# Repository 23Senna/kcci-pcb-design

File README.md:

# KCCI PCB Design Portfolio

PCB design work by **Bramantio Ananda** (Electrical Engineering, Institut Teknologi Bandung) during the
**KCCI Overseas Professional Technical Workforce Training Program – Electronics track**.
All boards were designed in **KiCad 10** from schematic capture through routing, DRC, and fabrication output.

| Project | Layers | Size | Highlights |
|---|---|---|---|
| [**ESP32-P4 MIPI-DSI → HDMI / LVDS Bridge**](hdmi-lvds-bridge/) | 4 | 65.4 × 49.2 mm | LT8912B bridge, 100 Ω controlled-impedance pairs, length-matched DSI / TMDS / LVDS, double-sided assembly |
| [**ATmega128-16A Minimum System**](atmega128-minimum-system/) | 2 | 71.6 × 46.3 mm | TQFP-64 MCU, 5 V linear regulator, ISP header, all ports broken out |
| [**Conveyor Sorter Shield** (group project)](conveyor-shield-kel1/) | 2 | — | STM32 Nucleo-F411RE shield with buck converter and actuator connectors |
| [**Signal-Integrity Analyses**](signal-integrity/) | — | — | Crosstalk, backplane channel, and CTLE studies (MATLAB, Serial Link Designer, SPICE) |

## Repository layout

Each board folder follows the same structure:

```
<project>/
├── kicad/            KiCad project (.kicad_pro / .kicad_sch / .kicad_pcb) + project-local libraries
├── fabrication/
│   ├── gerber/       Gerber + Excellon drill files (ready to upload to a PCB fab)
│   └── assembly/     BOM (.csv) and pick-and-place (.pos)
└── docs/             Schematic PDF and board renders
```

## Opening the projects

1. Install [KiCad 10](https://www.kicad.org/download/) (files were saved with KiCad 10.0.7; older versions cannot open them).
2. Open `<project>/kicad/*.kicad_pro`.
   Custom symbols and footprints are included in each project's `kicad/library` folder and registered in the
   project-local `sym-lib-table` / `fp-lib-table`, so no extra library setup is needed.

## Author

Bramantio Ananda · [Portfolio](https://bramantio-ananda-portfolio.netlify.app/) · [GitHub @23Senna](https://github.com/23Senna)

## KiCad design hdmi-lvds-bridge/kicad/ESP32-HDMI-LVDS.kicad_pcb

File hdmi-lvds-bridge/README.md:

# ESP32-P4 MIPI-DSI → HDMI / LVDS Bridge

A 4-layer converter board that takes the **2-lane MIPI-DSI** display output of an **ESP32-P4** and drives either an
**HDMI** monitor or an **LVDS** panel, using the **Lontium LT8912B** bridge IC.

<p align="center"><sub>Top and bottom renders generated from the fabrication Gerbers.</sub></p>

## Block diagram

```mermaid
flowchart LR
    P4["ESP32-P4<br/>(MIPI-DSI host)"] -- "DSI CLK + D0/D1<br/>FFC J3" --> U2["LT8912B<br/>MIPI → HDMI/LVDS"]
    P4 -- "I²C · INT · RSTN · I²S<br/>(3.3 V)" --> LS["BSS138<br/>level shifters"] -- "1.8 V" --> U2
    U2 -- "TMDS CLK + D0–D2" --> ESD["RClamp0524P<br/>ESD"] --> J4["HDMI Type-A<br/>J4"]
    U2 -- "LVDS CLK + D0–D3" --> J2["LVDS header<br/>J2 (2×9)"]
    P4 -- "3.3 V" --> LDO["SGM2212<br/>1.8 V LDO"] -- "ferrite-isolated rails" --> U2
    J1["J1 · 5 V in"] --> D2["Schottky<br/>reverse protection"] -- "HDMI 5 V" --> J4
```

## Specifications

| Item | Value |
|---|---|
| Board size | 65.4 × 49.2 mm, 1.6 mm FR-4 |
| Stack-up | 4 layers – **F.Cu signal / In1 GND / In2 GND / B.Cu signal** (JLCPCB JLC04161H-7628, prepreg 0.21 mm, εr ≈ 4.4) |
| Components | 96 placements – 61 top, 35 bottom (double-sided assembly) |
| Differential pairs | 100 Ω: 0.1278 mm width / 0.127 mm gap (from JLCPCB impedance calculator) |
| Signal / power tracks | 0.2 mm (0.15 mm at QFN pins) / 0.5 mm |
| Vias | 0.6 mm pad / 0.3 mm drill |
| Min. clearance · copper-to-edge | 0.127 mm · 0.5 mm |

### Length matching (custom DRC rules in `ESP32-HDMI-LVDS.kicad_dru`)

| Interface | Pairs | Target length | Intra-pair skew |
|---|---|---|---|
| MIPI-DSI (J3 → LT8912B) | CLK, D0, D1 | 71.74 mm (±0.05) | ≤ 0.07 mm |
| HDMI TMDS (LT8912B → J4) | CLK, D0, D1, D2 | 12.76 mm (±0.14) | ≤ 0.10 mm |
| LVDS (LT8912B → J2) | CLK, D0–D3 | 18.70 mm (±0.04) | ≤ 0.04 mm |

All high-speed pairs run over the solid inner ground planes.

## Design notes

- **Power:** an SGM2212 LDO derives 1.8 V for the LT8912B from the ESP32-P4's 3.3 V rail, and each analog/digital/PLL rail
  is isolated with a 220 Ω @ 100 MHz ferrite bead plus 10 µF / 0.1 µF decoupling. 5 V enters on J1 through a 1N5819
  Schottky (reverse-polarity protection) and supplies the HDMI +5 V / DDC side.
  The decoupling capacitors sit on the bottom side directly under U2.
- **Clock and PLL:** 25 MHz crystal (10 pF load caps, 1 MΩ bias), 6.04 kΩ R6K bias resistor, and a 2.2 nF HDMI-PLL
  loop-filter capacitor on PLL_LPF (pin 35).
- **Control signals:** BSS138 bidirectional shifters translate I²C, INT, RSTN, and I²S between the ESP32-P4 (3.3 V) and the
  LT8912B (1.8 V). HDMI DDC is shifted to the 5 V HDMI side, and HPD is level-shifted through an MMBT3904.
- **Protection:** RClamp0524P TVS arrays on all TMDS lines at the HDMI connector.

## Files

| Path | Contents |
|---|---|
| [`kicad/`](kicad/) | KiCad 10 project, custom DRC rules, project-local symbol / footprint / 3D libraries |
| [`fabrication/gerber/`](fabrication/gerber/) | Gerbers (F/In1/In2/B copper, mask, paste, silk, edge) and PTH / NPTH drill files |
| [`fabrication/assembly/`](fabrication/assembly/) | BOM (`ESP32-HDMI-LVDS-BOM.csv`) and pick-and-place (`ESP32-HDMI-LVDS-all.pos`) |
| [`docs/`](docs/) | Schematic PDF (exported 2026-10-15) and board renders |

**Status:** design complete, DRC-clean in KiCad 10.

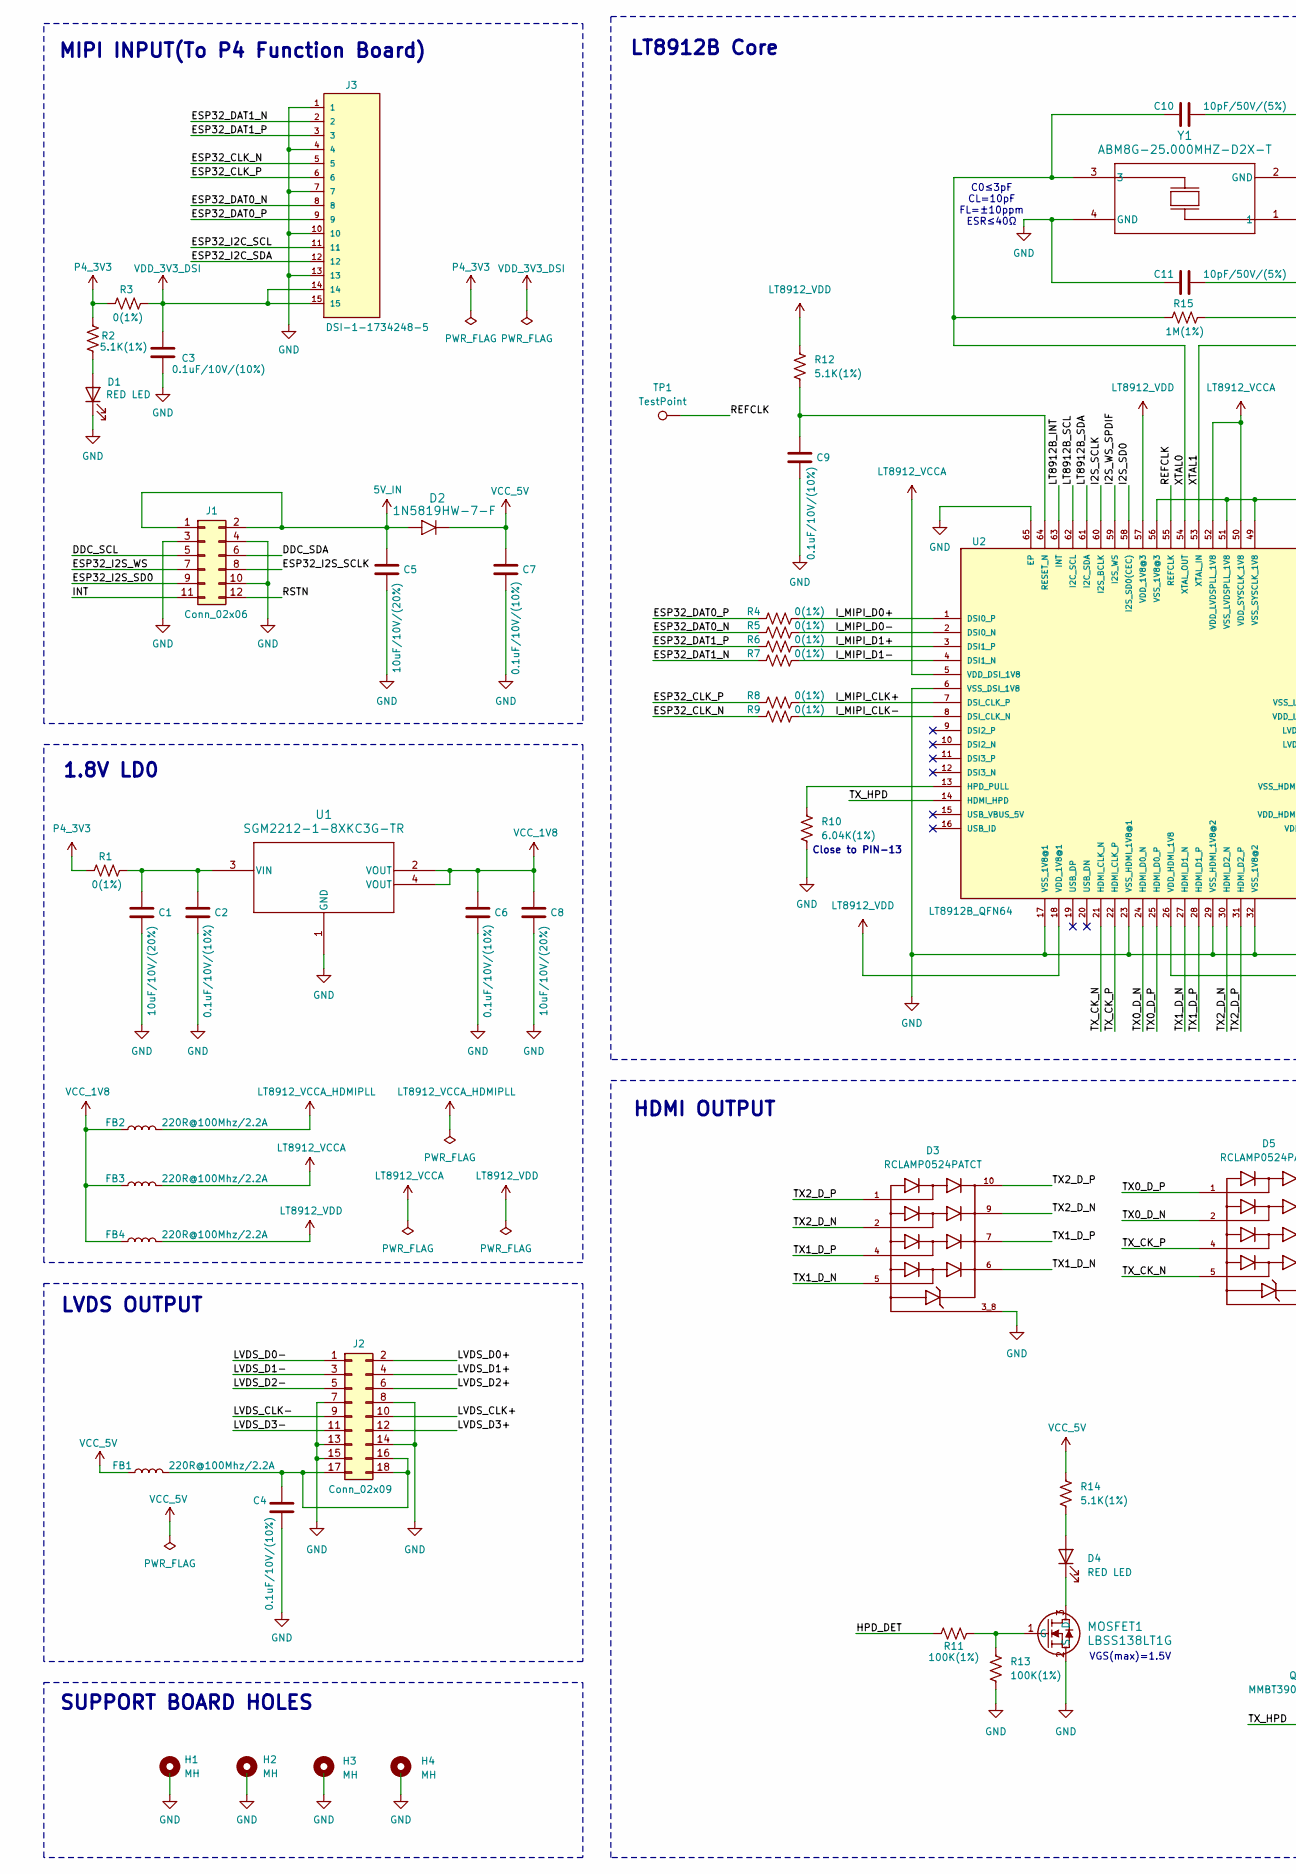
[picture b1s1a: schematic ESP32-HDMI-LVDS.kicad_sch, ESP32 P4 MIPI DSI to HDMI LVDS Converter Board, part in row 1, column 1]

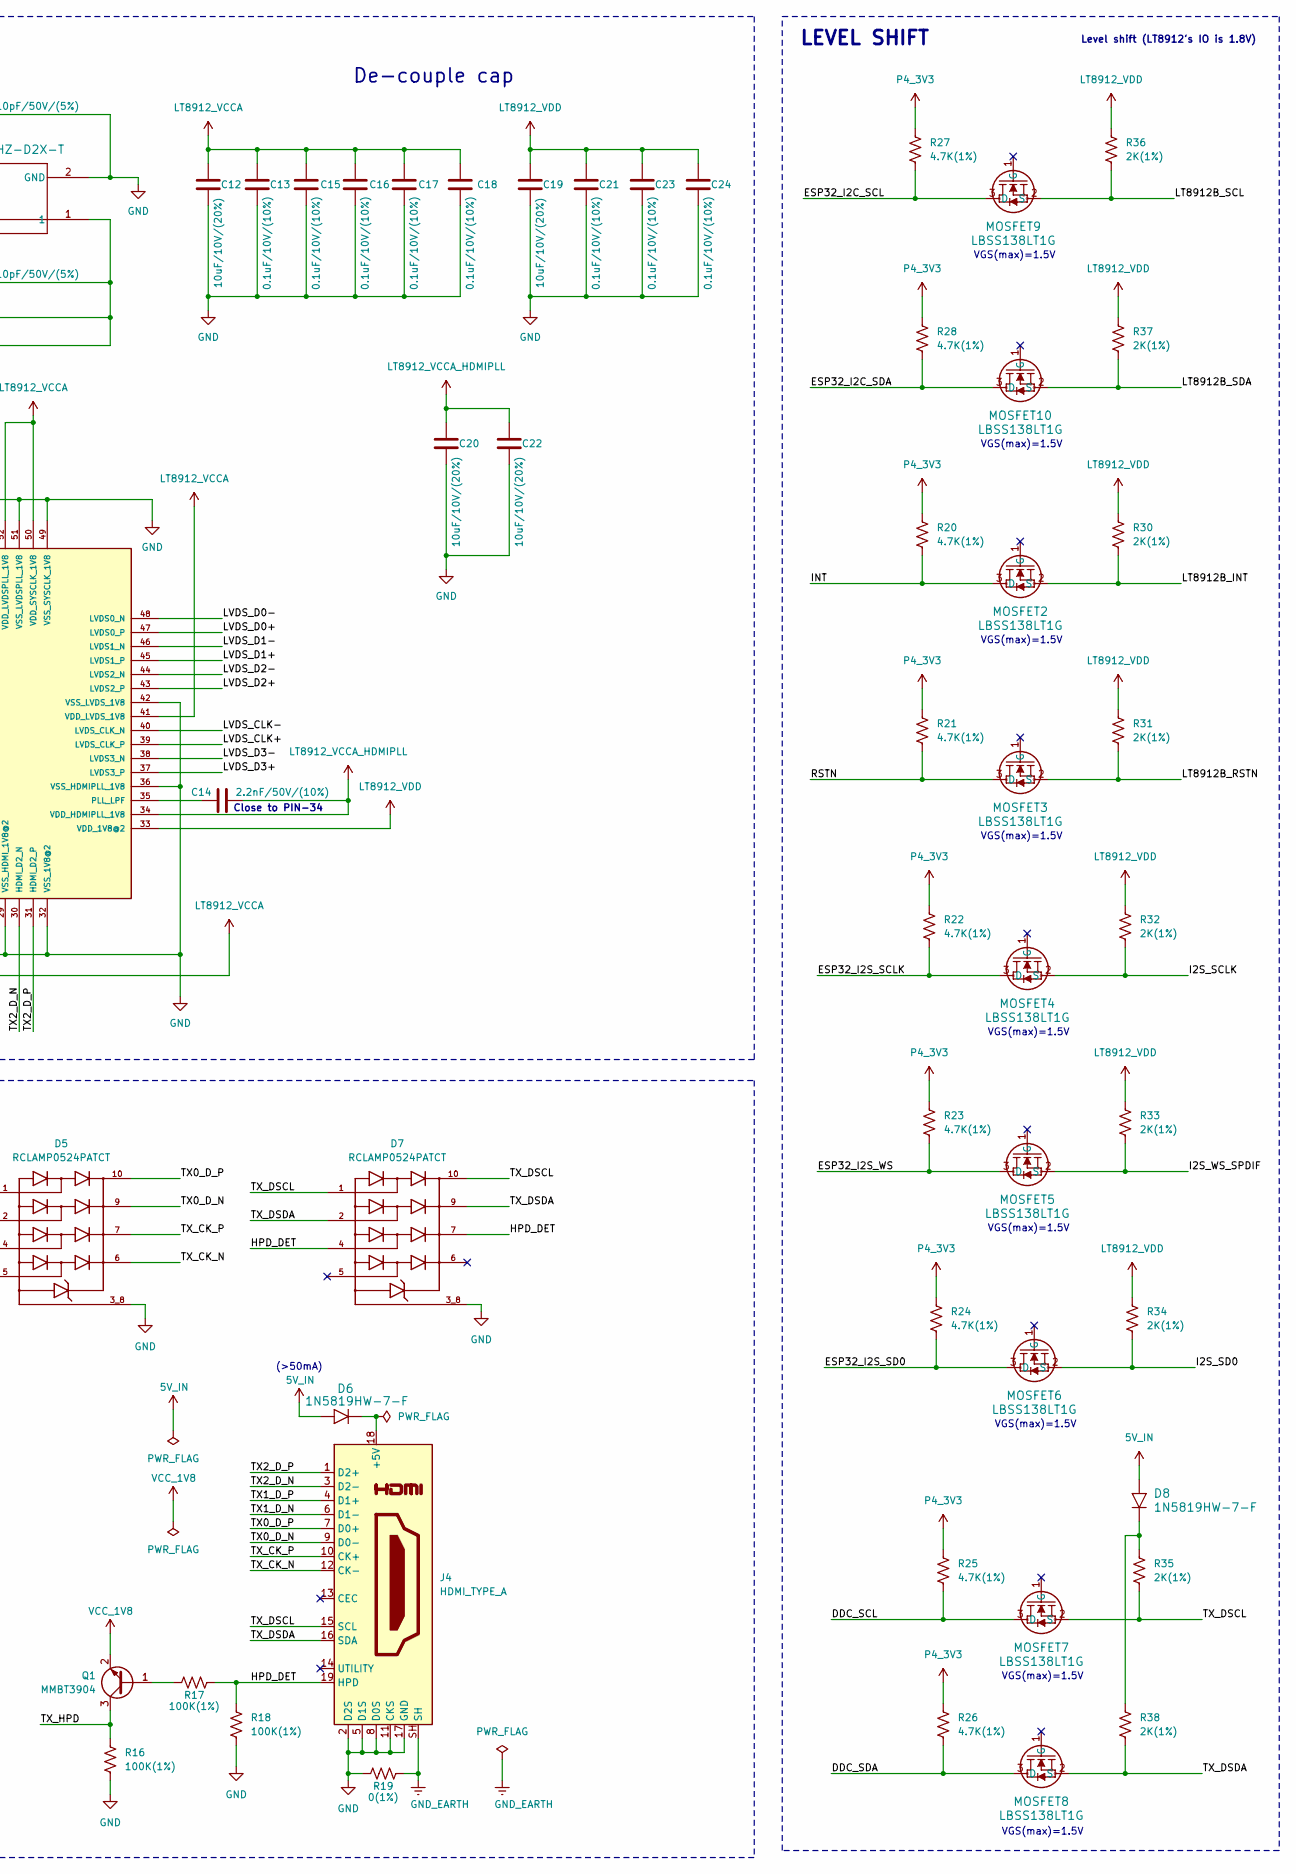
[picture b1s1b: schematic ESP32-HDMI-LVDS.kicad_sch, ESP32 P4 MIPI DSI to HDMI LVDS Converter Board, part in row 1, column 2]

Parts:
C1, C5, C8, C12, C19, C20, C22: 10uF/10V/(20%); C_0603_1608Metric_Pad1.08x0.95mm_HandSolder
C2, C3, C4, C6, C7, C9, C13, C15, C16, C17, C18, C21, C23, C24: 0.1uF/10V/(10%); C_0603_1608Metric_Pad1.08x0.95mm_HandSolder
C10, C11: 10pF/50V/(5%); C_0603_1608Metric_Pad1.08x0.95mm_HandSolder
C14: 2.2nF/50V/(10%); C_0603_1608Metric_Pad1.08x0.95mm_HandSolder
D1, D4: RED LED; LED_0603_1608Metric_Pad1.05x0.95mm_HandSolder
D2, D6, D8: 1N5819HW-7-F; 1N5819HW-7-F_DIO
D3, D5, D7: RCLAMP0524PATCT; DIO_RCLAMP0524PATCT; PARTREV 2/23/2011
FB1, FB2, FB3, FB4: 220R@100Mhz/2.2A; L_0603_1608Metric_Pad1.05x0.95mm_HandSolder
H1, H2, H3, H4: MH; MountingHole_3.2mm_M3_Pad_TopBottom
J1: Conn_02x06; PinHeader_2x06_P2.54mm_Vertical
J2: Conn_02x09; PinHeader_2x09_P2.54mm_Vertical
J3: DSI-1-1734248-5; TE_1-1734248-5; PARTREV E1
J4: HDMI_TYPE_A; HDMI_A_Molex_208658-1001_Horizontal
MOSFET1, MOSFET2, MOSFET3, MOSFET4, MOSFET5, MOSFET6, MOSFET7, MOSFET8, MOSFET9, MOSFET10: LBSS138LT1G; SOT23_TO-236_LRC
Q1: MMBT3904; SOT-23
R1, R3, R4, R5, R6, R7, R8, R9, R19: 0(1%); R_0603_1608Metric_Pad0.98x0.95mm_HandSolder
R2, R12, R14: 5.1K(1%); R_0603_1608Metric_Pad0.98x0.95mm_HandSolder
R10: 6.04K(1%); R_0603_1608Metric_Pad0.98x0.95mm_HandSolder
R11, R13, R16, R17, R18: 100K(1%); R_0603_1608Metric_Pad0.98x0.95mm_HandSolder
R15: 1M(1%); R_0603_1608Metric_Pad0.98x0.95mm_HandSolder
R20, R21, R22, R23, R24, R25, R26, R27, R28: 4.7K(1%); R_0603_1608Metric_Pad0.98x0.95mm_HandSolder
R30, R31, R32, R33, R34, R35, R36, R37, R38: 2K(1%); R_0603_1608Metric_Pad0.98x0.95mm_HandSolder
TP1: TestPoint; TestPoint_Pad_D1.0mm
U1: SGM2212-1-8XKC3G-TR; SOT-223-3_SGM2212_SNC
U2: LT8912B_QFN64; LT8912B
Y1: ABM8G-25.000MHZ-D2X-T; CRYSTAL_ABM8G_ABR

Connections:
5V_IN: C5.2, D2.1 (A), D6.1 (A), D8.1 (A), J1.1, J1.2
/DDC_SCL: J1.5, MOSFET7.3 (D), R25.2
/DDC_SDA: J1.6, MOSFET8.3 (D), R26.2
/ESP32_CLK_N: J3.5, J3.5_1 (5), R9.1
/ESP32_CLK_P: J3.6, J3.6_1 (6), R8.1
/ESP32_DAT0_N: J3.8, J3.8_1 (8), R5.1
/ESP32_DAT0_P: J3.9, J3.9_1 (9), R4.1
/ESP32_DAT1_N: J3.2, J3.2_1 (2), R7.1
/ESP32_DAT1_P: J3.3, J3.3_1 (3), R6.1
/ESP32_I2C_SCL: J3.11, J3.11_1 (11), MOSFET9.3 (D), R27.2
/ESP32_I2C_SDA: J3.12, J3.12_1 (12), MOSFET10.3 (D), R28.2
/ESP32_I2S_SCLK: J1.8, MOSFET4.3 (D), R22.2
/ESP32_I2S_SD0: J1.9, MOSFET6.3 (D), R24.2
/ESP32_I2S_WS: J1.7, MOSFET5.3 (D), R23.2
/HPD_DET: D7.4, D7.7, J4.19 (HPD), R11.1, R17.2, R18.1
/I2S_SCLK: MOSFET4.2 (S), R32.2, U2.60 (I2S_BCLK)
/I2S_SD0: MOSFET6.2 (S), R34.2, U2.58 (I2S_SD0(CEC))
/I2S_WS_SPDIF: MOSFET5.2 (S), R33.2, U2.59 (I2S_WS)
/INT: J1.11, MOSFET2.3 (D), R20.2
/I_MIPI_CLK+: R8.2, U2.7 (DSI_CLK_P)
/I_MIPI_CLK-: R9.2, U2.8 (DSI_CLK_N)
/I_MIPI_D0+: R4.2, U2.1 (DSI0_P)
/I_MIPI_D0-: R5.2, U2.2 (DSI0_N)
/I_MIPI_D1+: R6.2, U2.3 (DSI1_P)
/I_MIPI_D1-: R7.2, U2.4 (DSI1_N)
/LT8912B_INT: MOSFET2.2 (S), R30.2, U2.63 (INT)
/LT8912B_RSTN: MOSFET3.2 (S), R31.2
/LT8912B_SCL: MOSFET9.2 (S), R36.2, U2.62 (I2C_SCL)
/LT8912B_SDA: MOSFET10.2 (S), R37.2, U2.61 (I2C_SDA)
/LVDS_CLK+: J2.10, U2.39 (LVDS_CLK_P)
/LVDS_CLK-: J2.9, U2.40 (LVDS_CLK_N)
/LVDS_D0+: J2.2, U2.47 (LVDS0_P)
/LVDS_D0-: J2.1, U2.48 (LVDS0_N)
/LVDS_D1+: J2.4, U2.45 (LVDS1_P)
/LVDS_D1-: J2.3, U2.46 (LVDS1_N)
/LVDS_D2+: J2.6, U2.43 (LVDS2_P)
/LVDS_D2-: J2.5, U2.44 (LVDS2_N)
/LVDS_D3+: J2.12, U2.37 (LVDS3_P)
/LVDS_D3-: J2.11, U2.38 (LVDS3_N)
/REFCLK: TP1.1 (1_1), U2.55 (REFCLK)
/RSTN: J1.12, MOSFET3.3 (D), R21.2
/TX0_D_N: D5.2, D5.9, J4.9 (D0-), U2.24 (HDMI_D0_N)
/TX0_D_P: D5.1, D5.10, J4.7 (D0+), U2.25 (HDMI_D0_P)
/TX1_D_N: D3.5, D3.6, J4.6 (D1-), U2.27 (HDMI_D1_N)
/TX1_D_P: D3.4, D3.7, J4.4 (D1+), U2.28 (HDMI_D1_P)
/TX2_D_N: D3.2, D3.9, J4.3 (D2-), U2.30 (HDMI_D2_N)
/TX2_D_P: D3.1, D3.10, J4.1 (D2+), U2.31 (HDMI_D2_P)
/TX_CK_N: D5.5, D5.6, J4.12 (CK-), U2.21 (HDMI_CLK_N)
/TX_CK_P: D5.4, D5.7, J4.10 (CK+), U2.22 (HDMI_CLK_P)
/TX_DSCL: D7.1, D7.10, J4.15 (SCL), MOSFET7.2 (S), R35.2
/TX_DSDA: D7.2, D7.9, J4.16 (SDA), MOSFET8.2 (S), R38.2
/TX_HPD: Q1.3 (C), R16.1, U2.14 (HDMI_HPD)
/XTAL0: C10.1, R15.1, U2.54 (XTAL_OUT), Y1.3
/XTAL1: C11.2, R15.2, U2.53 (XTAL_IN), Y1.1
GND: C1.1, C2.1, C3.2, C4.2, C5.1, C6.1, C7.1, C8.1, C9.1, C10.2, C11.1, C12.1, C13.1, C15.1, C16.1, C17.1, C18.1, C19.1, C20.1, C21.1, C22.1, C23.1, C24.1, D1.1 (K), D3.3_8, D5.3_8, D7.3_8, J1.3, J1.4, J1.10, J2.7, J2.8, J2.13, J2.14, J2.15, J3.1, J3.1_1 (1), J3.4, J3.4_1 (4), J3.7, J3.7_1 (7), J3.10, J3.10_1 (10), J3.13, J3.13_1 (13), J4.2 (D2S), J4.5 (D1S), J4.8 (D0S), J4.11 (CKS), J4.17 (GND), MOSFET1.2 (S), R10.2, R13.2, R16.2, R18.2, R19.1, U1.1 (GND), U2.6 (VSS_DSI_1V8), U2.17 (VSS_1V8@1), U2.23 (VSS_HDMI_1V8@1), U2.29 (VSS_HDMI_1V8@2), U2.32 (VSS_1V8@2), U2.36 (VSS_HDMIPLL_1V8), U2.42 (VSS_LVDS_1V8), U2.49 (VSS_SYSCLK_1V8), U2.51 (VSS_LVDSPLL_1V8), U2.56 (VSS_1V8@3), U2.65 (EP), Y1.2 (GND), Y1.4 (GND)
GND_EARTH: J4.SH, R19.2
LT8912_VCCA: C12.2, C13.2, C15.2, C16.2, C17.2, C18.2, FB3.2, U2.5 (VDD_DSI_1V8), U2.26 (VDD_HDMI_1V8), U2.41 (VDD_LVDS_1V8), U2.50 (VDD_SYSCLK_1V8), U2.52 (VDD_LVDSPLL_1V8)
LT8912_VCCA_HDMIPLL: C14.2, C20.2, C22.2, FB2.2, U2.34 (VDD_HDMIPLL_1V8)
LT8912_VDD: C19.2, C21.2, C23.2, C24.2, FB4.2, R12.1, R30.1, R31.1, R32.1, R33.1, R34.1, R36.1, R37.1, U2.18 (VDD_1V8@1), U2.33 (VDD_1V8@2), U2.57 (VDD_1V8@3)
unnamed: D1.2 (A), R2.2
unnamed: D4.2 (A), R14.2
unnamed: D4.1 (K), MOSFET1.3 (D)
unnamed: D6.2 (K), J4.18 (+5V)
unnamed: D8.2 (K), R35.1, R38.1
unnamed: C4.1, FB1.2, J2.16, J2.17, J2.18
unnamed: MOSFET1.1 (G), R11.2, R13.1
unnamed: Q1.1 (B), R17.1
unnamed: C1.2, C2.2, R1.2, U1.3 (VIN)
unnamed: R10.1, U2.13 (HPD_PULL)
unnamed: C14.1, U2.35 (PLL_LPF)
unnamed: C9.2, R12.2, U2.64 (RESET_N)
P4_3V3: R1.1, R2.1, R3.1, R20.1, R21.1, R22.1, R23.1, R24.1, R25.1, R26.1, R27.1, R28.1
VCC_1V8: C6.2, C8.2, FB2.1, FB3.1, FB4.1, Q1.2 (E), U1.2 (VOUT), U1.4 (VOUT)
VCC_5V: C7.2, D2.2 (K), FB1.1, R14.1
VDD_3V3_DSI: C3.1, J3.14, J3.14_1 (14), J3.15, J3.15_1 (15), R3.2

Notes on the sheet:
HDMI OUTPUT
VGS(max)=1.5V
Level shift (LT8912's IO is 1.8V)
Close to PIN-13
1.8V LD0
(>50mA)
Close to PIN-34
De-couple cap
LT8912B Core
C0≤3pF CL=10pF FL=±10ppm ESR≤40Ω
SUPPORT BOARD HOLES
MIPI INPUT(To P4 Function Board)
LVDS OUTPUT
LEVEL SHIFT

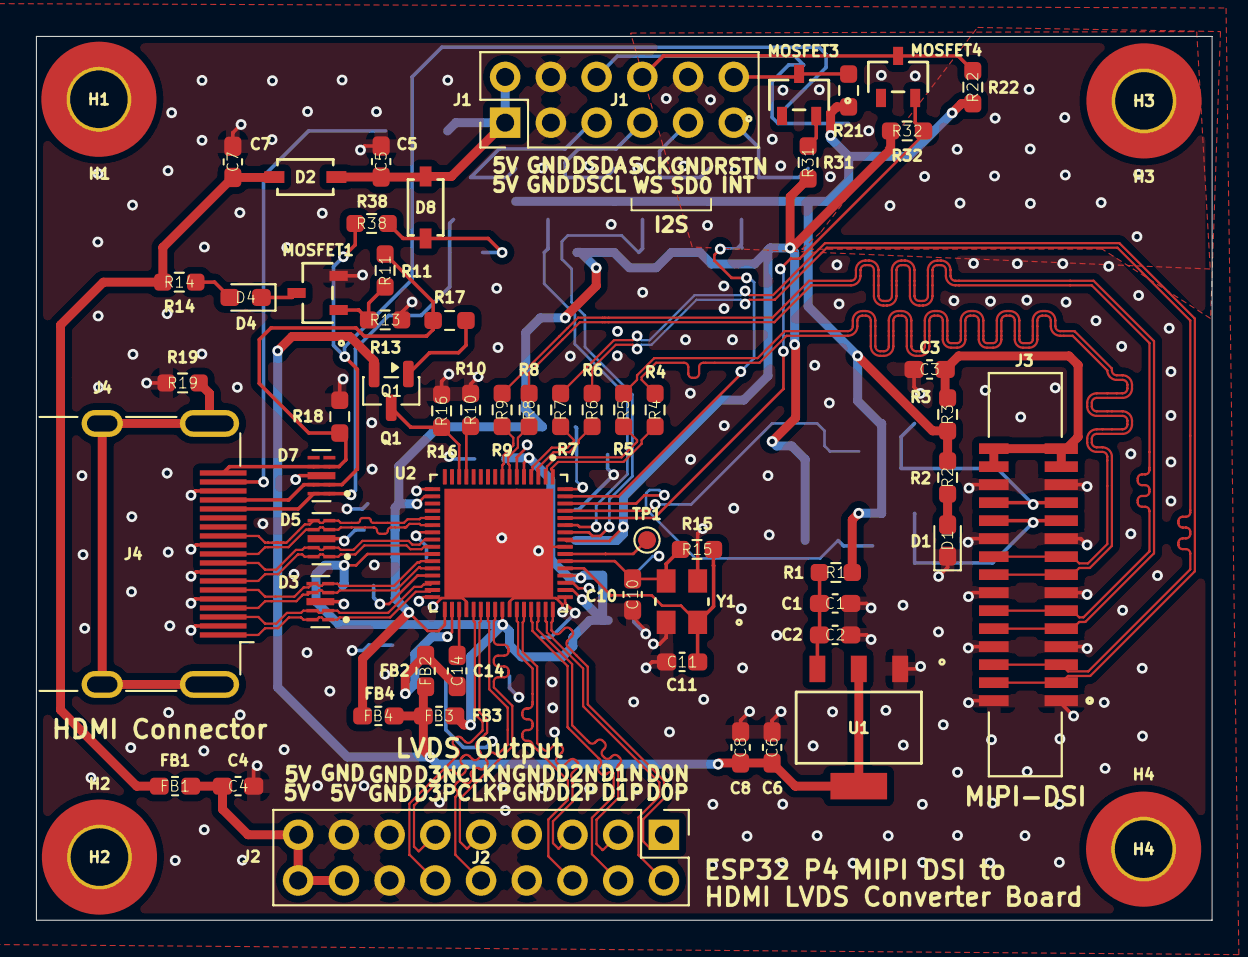
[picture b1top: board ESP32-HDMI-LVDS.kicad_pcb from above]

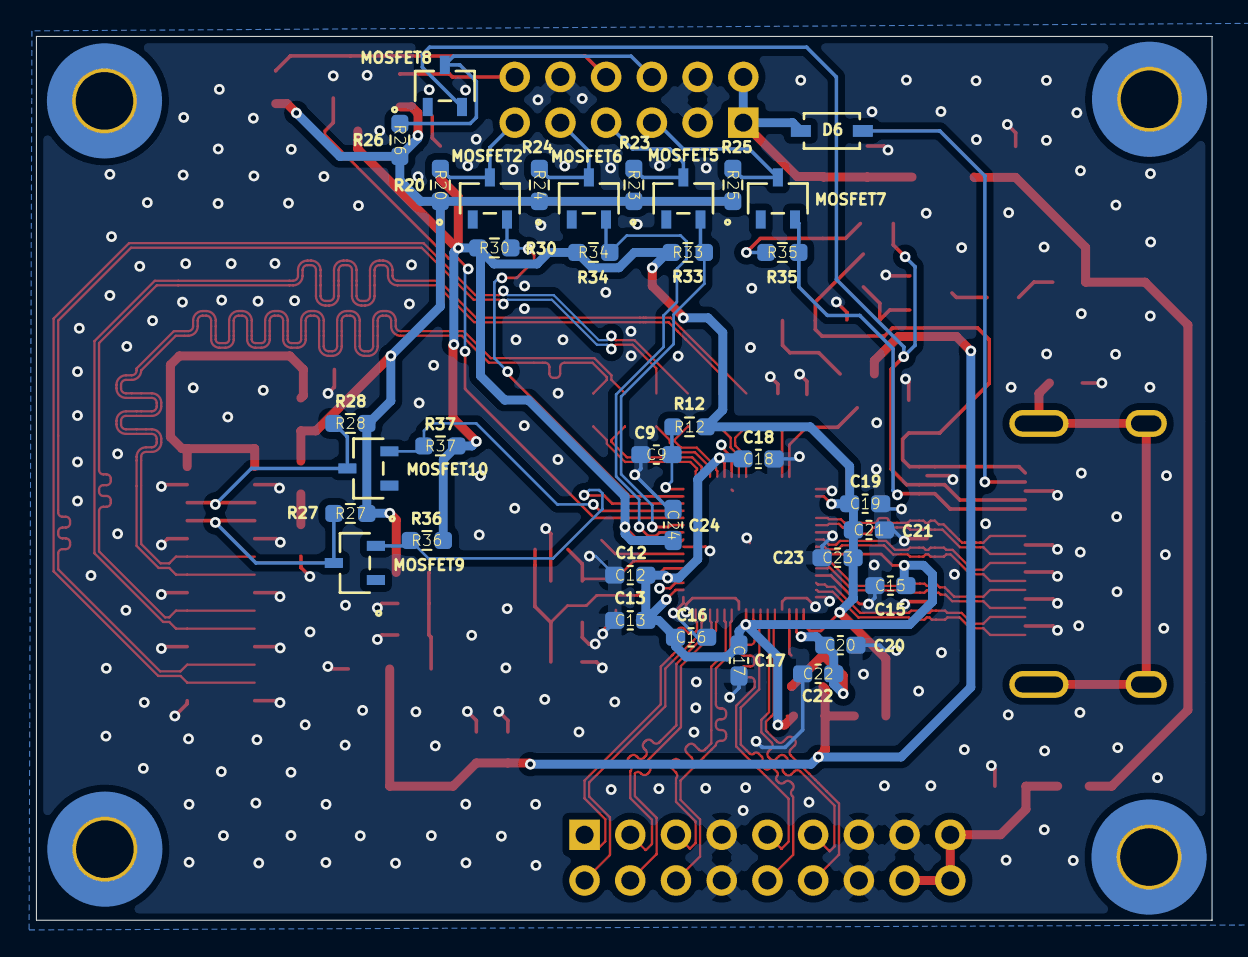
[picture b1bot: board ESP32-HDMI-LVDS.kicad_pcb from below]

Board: 4 copper layers, 65.3 x 49.1 mm, 96 parts (35 on the bottom side), 75 nets.

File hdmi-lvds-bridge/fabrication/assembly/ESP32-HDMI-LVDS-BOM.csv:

"Reference","Qty","Value","DNP","Exclude from BOM","Exclude from Board","Footprint","Datasheet"
"C1,C5,C8,C12,C19,C20,C22","7","10uF/10V/(20%)","","","","Capacitor_SMD:C_0603_1608Metric_Pad1.08x0.95mm_HandSolder",""
"C2,C3,C4,C6,C7,C9,C13,C15,C16,C17,C18,C21,C23,C24","14","0.1uF/10V/(10%)","","","","Capacitor_SMD:C_0603_1608Metric_Pad1.08x0.95mm_HandSolder",""
"C10,C11","2","10pF/50V/(5%)","","","","Capacitor_SMD:C_0603_1608Metric_Pad1.08x0.95mm_HandSolder",""
"C14","1","2.2nF/50V/(10%)","","","","Capacitor_SMD:C_0603_1608Metric_Pad1.08x0.95mm_HandSolder",""
"D1,D4","2","RED LED","","","","LED_SMD:LED_0603_1608Metric_Pad1.05x0.95mm_HandSolder",""
"D2,D6,D8","3","1N5819HW-7-F","","","","1N5819HW-7-F:1N5819HW-7-F_DIO","1N5819HW-7-F"
"D3,D5,D7","3","RCLAMP0524PATCT","","","","RCLAMP0524PATCT:DIO_RCLAMP0524PATCT",""
"FB1,FB2,FB3,FB4","4","220R@100Mhz/2.2A","","","","Inductor_SMD:L_0603_1608Metric_Pad1.05x0.95mm_HandSolder",""
"J1","1","Conn_02x06","","","","Connector_PinHeader_2.54mm:PinHeader_2x06_P2.54mm_Vertical",""
"J2","1","Conn_02x09","","","","Connector_PinHeader_2.54mm:PinHeader_2x09_P2.54mm_Vertical",""
"J3","1","DSI-1-1734248-5","","","","1-1734248-5:TE_1-1734248-5",""
"J4","1","HDMI_TYPE_A","","","","hdmi_type_a:HDMI_A_Molex_208658-1001_Horizontal","https://en.wikipedia.org/wiki/HDMI"
"MOSFET1,MOSFET2,MOSFET3,MOSFET4,MOSFET5,MOSFET6,MOSFET7,MOSFET8,MOSFET9,MOSFET10","10","LBSS138LT1G","","","","LBSS138LT1G:SOT23_TO-236_LRC","LBSS138LT1G"
"Q1","1","MMBT3904","","","","Package_TO_SOT_SMD:SOT-23","https://www.onsemi.com/pdf/datasheet/pzt3904-d.pdf"
"R1,R3,R4,R5,R6,R7,R8,R9,R19","9","0(1%)","","","","Resistor_SMD:R_0603_1608Metric_Pad0.98x0.95mm_HandSolder",""
"R2,R12,R14","3","5.1K(1%)","","","","Resistor_SMD:R_0603_1608Metric_Pad0.98x0.95mm_HandSolder",""
"R10","1","6.04K(1%)","","","","Resistor_SMD:R_0603_1608Metric_Pad0.98x0.95mm_HandSolder",""
"R11,R13,R16,R17,R18","5","100K(1%)","","","","Resistor_SMD:R_0603_1608Metric_Pad0.98x0.95mm_HandSolder",""
"R15","1","1M(1%)","","","","Resistor_SMD:R_0603_1608Metric_Pad0.98x0.95mm_HandSolder",""
"R20,R21,R22,R23,R24,R25,R26,R27,R28","9","4.7K(1%)","","","","Resistor_SMD:R_0603_1608Metric_Pad0.98x0.95mm_HandSolder",""
"R30,R31,R32,R33,R34,R35,R36,R37,R38","9","2K(1%)","","","","Resistor_SMD:R_0603_1608Metric_Pad0.98x0.95mm_HandSolder",""
"TP1","1","TestPoint","","","","TestPoint:TestPoint_Pad_D1.0mm",""
"U1","1","SGM2212-1-8XKC3G-TR","","","","SGM2212-1-8XKC3G-TR:SOT-223-3_SGM2212_SNC","SGM2212-1-8XKC3G-TR"
"U2","1","LT8912B_QFN64","","","","LT8912B:LT8912B",""
"Y1","1","ABM8G-25.000MHZ-D2X-T","","","","XTAL3225:CRYSTAL_ABM8G_ABR","ABM8G-25.000MHZ-D2X-T"

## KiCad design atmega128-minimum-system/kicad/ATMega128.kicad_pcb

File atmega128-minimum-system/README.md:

# ATmega128-16A Minimum System

A 2-layer development board for the **Microchip ATmega128-16A** (TQFP-64): on-board 5 V regulation, a 16 MHz clock, an
AVR-ISP programming header, and every I/O port broken out to 2.54 mm headers.

<p align="center"><sub>Top and bottom renders generated from the fabrication Gerbers.</sub></p>

## Specifications

| Item | Value |
|---|---|
| Board size | 71.6 × 46.3 mm, 1.6 mm FR-4 |
| Layers | 2 (F.Cu / B.Cu) |
| Components | 28 placements, all on the top side |
| Tracks | 0.2 mm signal, 0.5 mm power |
| Vias | 0.6 mm pad / 0.3 mm drill |
| Copper-to-edge clearance | 0.5 mm |

## Circuit blocks

The schematic is split into three sections:

- **Power & regulator:** L7805 (TO-252) linear regulator with 47 µF input/output bulk capacitors, a slide switch, and an
  indicator LED.
- **ATmega128-16A core:** 16 MHz HC49 crystal with 22 pF load capacitors, four 0.1 µF decoupling capacitors, and a reset
  push-button with a 10 kΩ pull-up.
- **ISP & support:** 6-pin AVR-ISP header (PDI = PE0, PDO = PE1, SCK = PB1, RESET), seven 1×8 port headers, a second LED,
  and mounting holes.

## Files

| Path | Contents |
|---|---|
| [`kicad/`](kicad/) | KiCad 10 project (standard KiCad libraries only) |
| [`fabrication/gerber/`](fabrication/gerber/) | Gerbers and PTH / NPTH drill files |
| [`fabrication/assembly/`](fabrication/assembly/) | BOM (`ATMega128-BOM.csv`) and pick-and-place (`ATMega128-all.pos`) |
| [`docs/images/`](docs/images/) | Board renders |

**Status:** design complete, DRC-clean in KiCad 10.

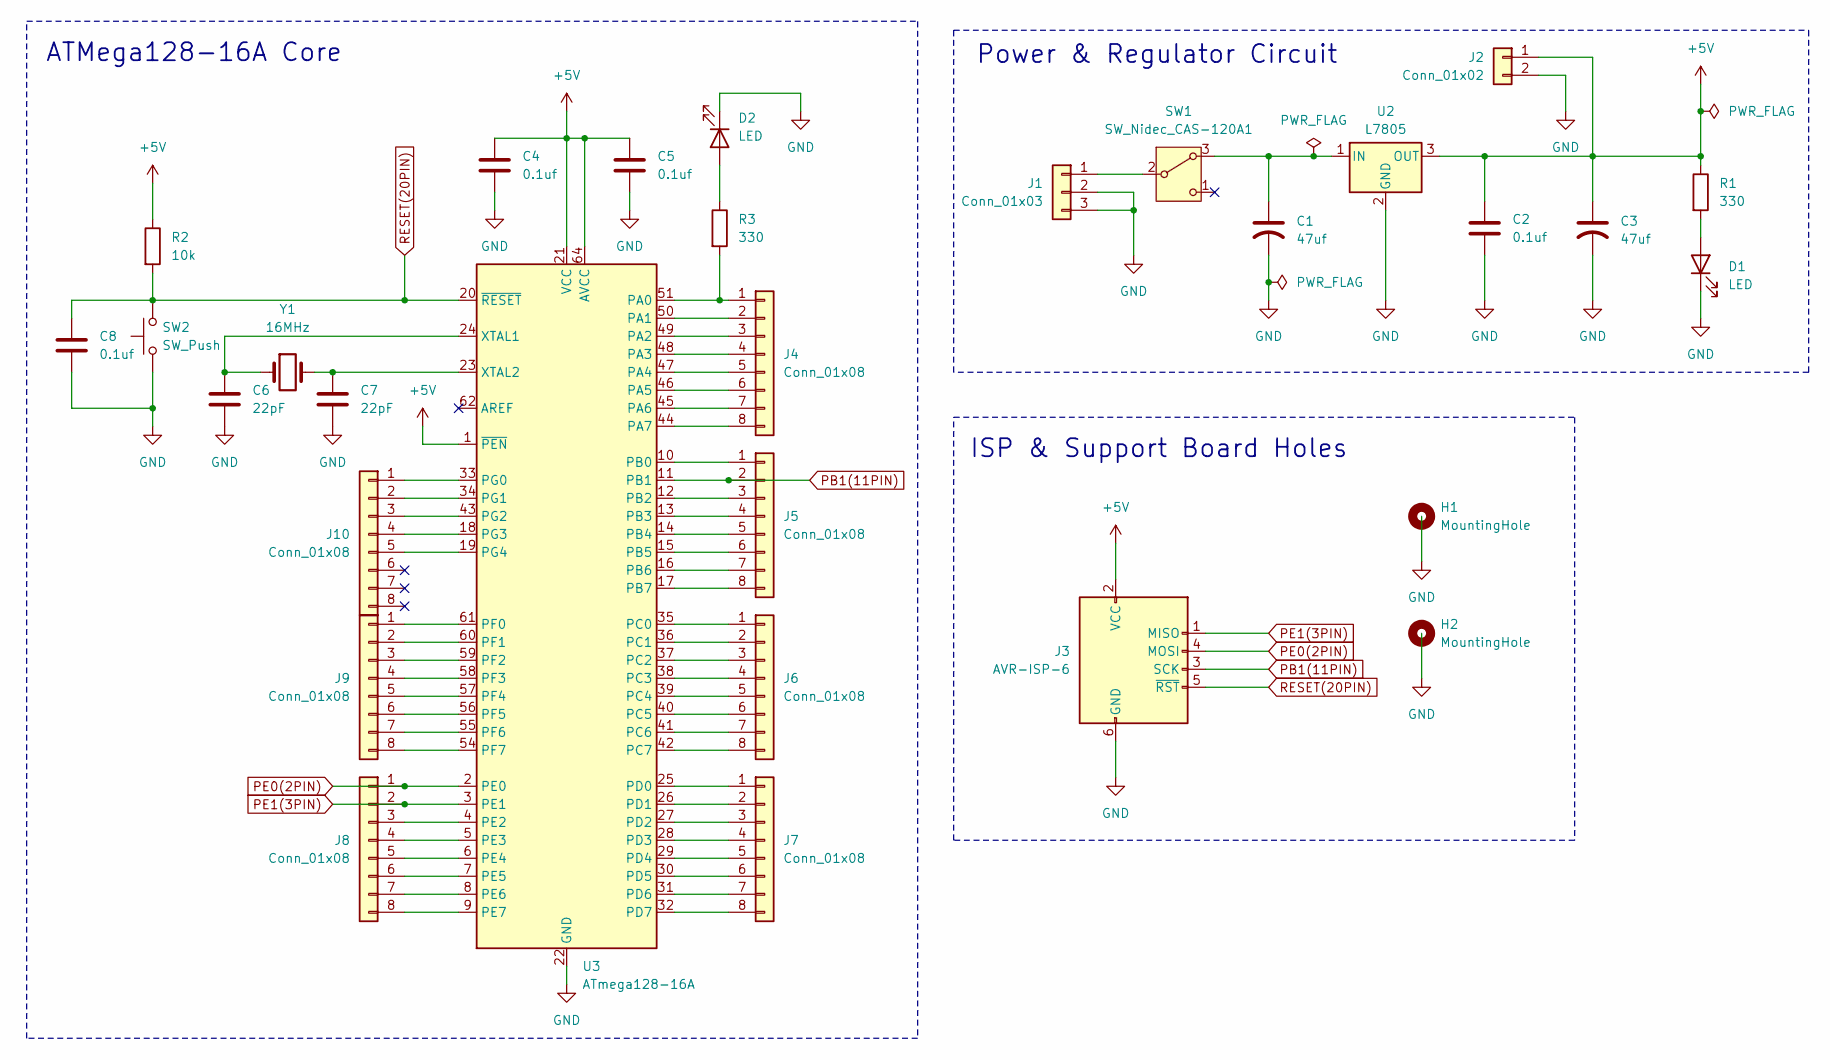
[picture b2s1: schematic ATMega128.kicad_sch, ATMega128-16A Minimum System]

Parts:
C1, C3: 47uf; CP_Elec_6.3x5.4
C2, C4, C5, C8: 0.1uf; C_0805_2012Metric
C6, C7: 22pF; C_0805_2012Metric
D1, D2: LED; LED_0805_2012Metric
H1, H2: MountingHole; MountingHole_2.1mm
J1: Conn_01x03; PinHeader_1x03_P2.54mm_Vertical
J2: Conn_01x02; PinHeader_1x02_P2.54mm_Vertical
J3: AVR-ISP-6; PinHeader_2x03_P2.54mm_Vertical
J4, J5, J6, J7, J8, J9, J10: Conn_01x08; PinHeader_1x08_P2.54mm_Vertical
R1, R3: 330; R_0805_2012Metric
R2: 10k; R_0805_2012Metric
SW1: SW_Nidec_CAS-120A1; Nidec_Copal_CAS-120A
SW2: SW_Push; SW_SPST_B3S-1000
U2: L7805; TO-252-2
U3: ATmega128-16A; TQFP-64_14x14mm_P0.8mm
Y1: 16MHz; Crystal_SMD_HC49-SD

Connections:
+5V: C2.1, C3.1, C4.1, C5.1, J2.1, J3.2 (VCC), R1.1, R2.1, U2.3 (OUT), U3.1 (~PEN), U3.21 (VCC), U3.52 (VCC), U3.64 (AVCC)
GND: C1.2, C2.2, C3.2, C4.2, C5.2, C6.2, C7.2, C8.2, D1.1 (K), D2.1 (K), J1.2, J1.3, J2.2, J3.6 (GND), SW2.1, U2.2 (GND), U3.22 (GND), U3.53 (GND), U3.63 (GND)
unnamed: D1.2 (A), R1.2
unnamed: D2.2 (A), R3.1
unnamed: J1.1, SW1.2 (B)
unnamed: J4.1, R3.2, U3.51 (PA0)
unnamed: J4.2, U3.50 (PA1)
unnamed: J4.3, U3.49 (PA2)
unnamed: J4.4, U3.48 (PA3)
unnamed: J4.5, U3.47 (PA4)
unnamed: J4.6, U3.46 (PA5)
unnamed: J4.7, U3.45 (PA6)
unnamed: J4.8, U3.44 (PA7)
unnamed: J5.1, U3.10 (PB0)
unnamed: J5.3, U3.12 (PB2)
unnamed: J5.4, U3.13 (PB3)
unnamed: J5.5, U3.14 (PB4)
unnamed: J5.6, U3.15 (PB5)
unnamed: J5.7, U3.16 (PB6)
unnamed: J5.8, U3.17 (PB7)
unnamed: J6.1, U3.35 (PC0)
unnamed: J6.2, U3.36 (PC1)
unnamed: J6.3, U3.37 (PC2)
unnamed: J6.4, U3.38 (PC3)
unnamed: J6.5, U3.39 (PC4)
unnamed: J6.6, U3.40 (PC5)
unnamed: J6.7, U3.41 (PC6)
unnamed: J6.8, U3.42 (PC7)
unnamed: J7.1, U3.25 (PD0)
unnamed: J7.2, U3.26 (PD1)
unnamed: J7.3, U3.27 (PD2)
unnamed: J7.4, U3.28 (PD3)
unnamed: J7.5, U3.29 (PD4)
unnamed: J7.6, U3.30 (PD5)
unnamed: J7.7, U3.31 (PD6)
unnamed: J7.8, U3.32 (PD7)
unnamed: J8.3, U3.4 (PE2)
unnamed: J8.4, U3.5 (PE3)
unnamed: J8.5, U3.6 (PE4)
unnamed: J8.6, U3.7 (PE5)
unnamed: J8.7, U3.8 (PE6)
unnamed: J8.8, U3.9 (PE7)
unnamed: J9.1, U3.61 (PF0)
unnamed: J9.2, U3.60 (PF1)
unnamed: J9.3, U3.59 (PF2)
unnamed: J9.4, U3.58 (PF3)
unnamed: J9.5, U3.57 (PF4)
unnamed: J9.6, U3.56 (PF5)
unnamed: J9.7, U3.55 (PF6)
unnamed: J9.8, U3.54 (PF7)
unnamed: J10.1, U3.33 (PG0)
unnamed: J10.2, U3.34 (PG1)
unnamed: J10.3, U3.43 (PG2)
unnamed: J10.4, U3.18 (PG3)
unnamed: J10.5, U3.19 (PG4)
unnamed: C1.1, SW1.3 (A), U2.1 (IN)
unnamed: C6.1, U3.24 (XTAL1), Y1.1
unnamed: C7.1, U3.23 (XTAL2), Y1.2
PB1(11PIN): J3.3 (SCK), J5.2, U3.11 (PB1)
PE0(2PIN): J3.4 (MOSI), J8.1, U3.2 (PE0)
PE1(3PIN): J3.1 (MISO), J8.2, U3.3 (PE1)
RESET(20PIN): C8.1, J3.5 (~RST), R2.2, SW2.2, U3.20 (~RESET)

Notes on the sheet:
ATMega128-16A Core
Power & Regulator Circuit
ISP & Support Board Holes

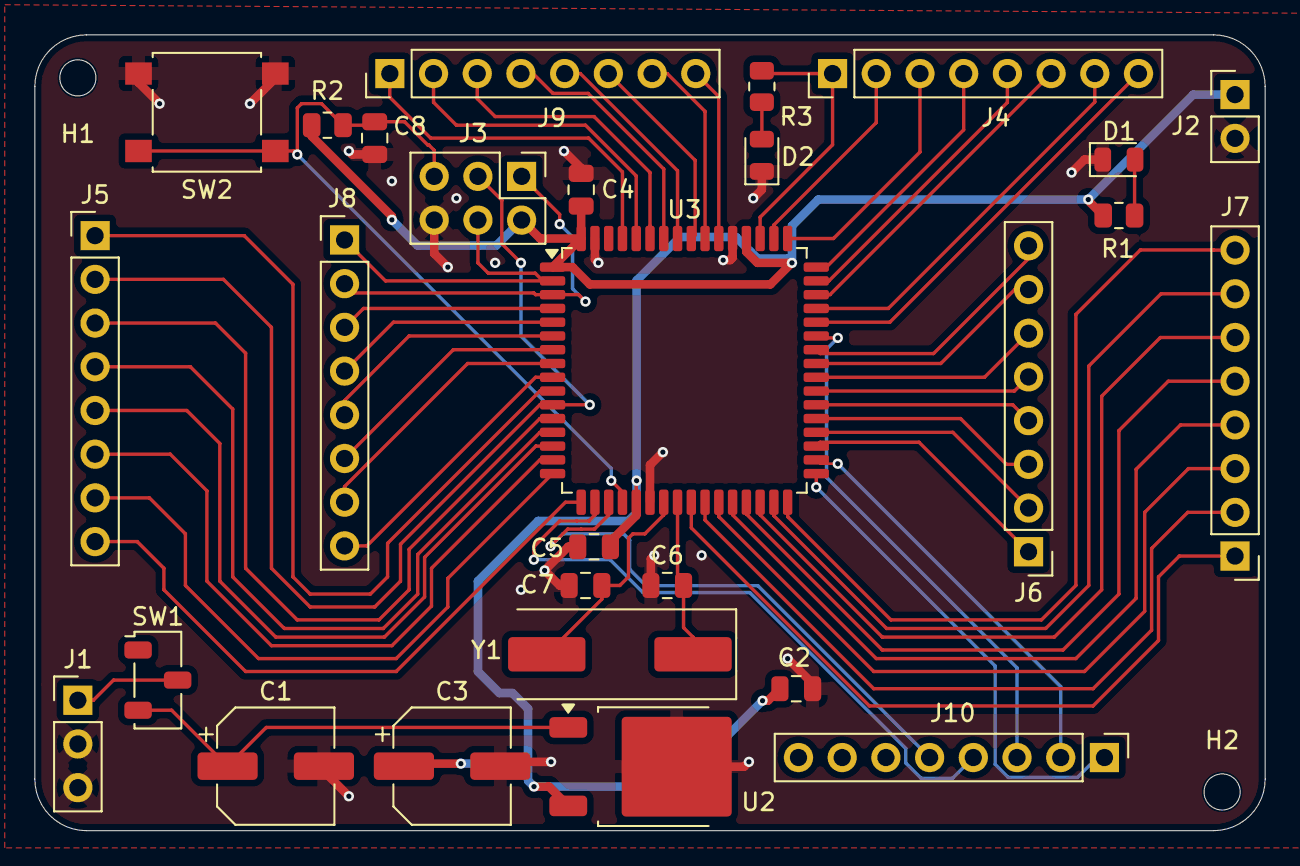
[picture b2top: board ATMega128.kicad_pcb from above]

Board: 2 copper layers, 71.5 x 46.2 mm, 30 parts (0 on the bottom side), 62 nets.

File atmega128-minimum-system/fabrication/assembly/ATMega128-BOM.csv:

"Reference","Qty","Value","DNP","Exclude from BOM","Exclude from Board","Footprint","Datasheet"
"C1,C3","2","47uf","","","","Capacitor_SMD:CP_Elec_6.3x5.4",""
"C2,C4,C5,C8","4","0.1uf","","","","Capacitor_SMD:C_0805_2012Metric",""
"C6,C7","2","22pF","","","","Capacitor_SMD:C_0805_2012Metric",""
"D1,D2","2","LED","","","","LED_SMD:LED_0805_2012Metric",""
"J1","1","Conn_01x03","","","","Connector_PinHeader_2.54mm:PinHeader_1x03_P2.54mm_Vertical",""
"J2","1","Conn_01x02","","","","Connector_PinHeader_2.54mm:PinHeader_1x02_P2.54mm_Vertical",""
"J3","1","AVR-ISP-6","","","","Connector_PinHeader_2.54mm:PinHeader_2x03_P2.54mm_Vertical",""
"J4,J5,J6,J7,J8,J9,J10","7","Conn_01x08","","","","Connector_PinHeader_2.54mm:PinHeader_1x08_P2.54mm_Vertical",""
"R1,R3","2","330","","","","Resistor_SMD:R_0805_2012Metric",""
"R2","1","10k","","","","Resistor_SMD:R_0805_2012Metric",""
"SW1","1","SW_Nidec_CAS-120A1","","","","Button_Switch_SMD:Nidec_Copal_CAS-120A","https://www.nidec-components.com/e/catalog/switch/cas.pdf"
"SW2","1","SW_Push","","","","Button_Switch_SMD:SW_SPST_B3S-1000",""
"U2","1","L7805","","","","Package_TO_SOT_SMD:TO-252-2","http://www.st.com/content/ccc/resource/technical/document/da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"
"U3","1","ATmega128-16A","","","","Package_QFP:TQFP-64_14x14mm_P0.8mm","http://ww1.microchip.com/downloads/en/DeviceDoc/doc2467.pdf"
"Y1","1","16MHz","","","","Crystal:Crystal_SMD_HC49-SD",""

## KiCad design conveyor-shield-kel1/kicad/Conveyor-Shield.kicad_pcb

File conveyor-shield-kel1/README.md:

# Conveyor Sorter Shield (Group 1)

> Group project – KCCI Firmware & PCB modules, Kelompok 1.

A 2-layer shield for the **STM32 Nucleo-F411RE** that powers and connects all peripherals of the conveyor-belt sorting
system built in the firmware module.

## Connections

| Ref | Connects to |
|---|---|
| J9 | 12 V input – main supply |
| Buck1 | LM2596 step-down module – 12 V → 5 V for the Nucleo and peripherals |
| J8 | BTS7960 DC conveyor-motor driver |
| J3 | Sorting-gate servo |
| J4 | Time-of-flight distance sensor |
| J1 | OLED display |
| J2 | Rotary encoder |
| J5 | Relay module |
| J6 / J7 | Start / Emergency buttons |
| SW1 | Nucleo reset button |

## Files

| Path | Contents |
|---|---|
| [`kicad/`](kicad/) | KiCad 10 project and the `Komponen_Kustom` symbol library |

The Nucleo and LM2596 footprints are embedded in the board file. The LM2596 3D model path points to a teammate's local
library, so it will show as missing in the 3D viewer; the PCB itself is unaffected.

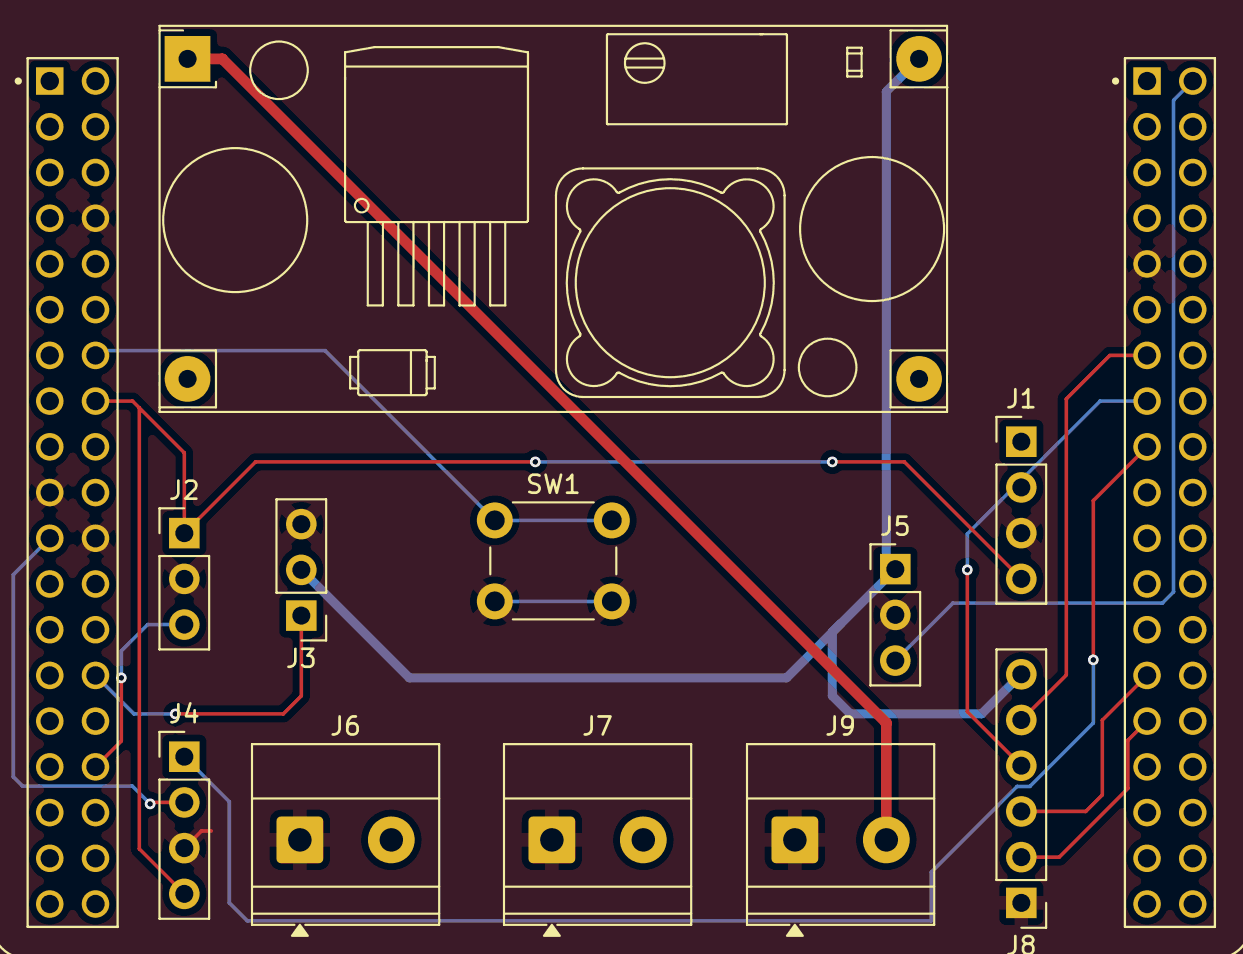
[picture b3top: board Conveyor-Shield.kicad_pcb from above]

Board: 2 copper layers, 12 parts (0 on the bottom side), 17 nets.

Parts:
Buck1: YAAJ_DCDC_StepDown_LM2596
J1: oled; PinHeader_1x04_P2.54mm_Vertical
J2: rotaryencoder; PinHeader_1x03_P2.54mm_Vertical
J3: SERVO; PinHeader_1x03_P2.54mm_Vertical
J4: tof40dc; PinHeader_1x04_P2.54mm_Vertical
J5: relay1; PinHeader_1x03_P2.54mm_Vertical
J6: Start Button; TerminalBlock_Phoenix_MKDS-1,5-2-5.08_1x02_P5.08mm_Horizont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
J7: Emergency Button; TerminalBlock_Phoenix_MKDS-1,5-2-5.08_1x02_P5.08mm_Horizont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
J8: UBTS7960; PinHeader_1x06_P2.54mm_Vertical
J9: 12V Input; TerminalBlock_Phoenix_MKDS-1,5-2-5.08_1x02_P5.08mm_Horizont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
SW1: reset button; SW_PUSH_6mm
U1: NUCLEO-F411RE; BOARD_NUCLEO-F411RE

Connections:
+5V: J3.2, J5.1, J8.6
GND: J1.3, J2.2, J3.3, J4.3, J5.2, J6.1, J7.1, J8.1, J9.1, SW1.2, U1.CN7_8 (GND_8), U1.CN7_19 (GND_19), U1.CN7_22 (GND_22), U1.CN10_9 (GND_9)
unnamed: J1.1, U1.CN10_5 (PB9)
unnamed: J1.2, U1.CN10_25 (PB10)
unnamed: J1.4, J2.1, J4.4, U1.CN7_16 (+3V3)
unnamed: J2.3, U1.CN7_32 (PA4)
unnamed: J3.1, U1.CN7_28 (PA0)
unnamed: J4.1, U1.CN10_17 (PB6)
unnamed: J4.2, U1.CN7_21 (PB7)
unnamed: J5.3, U1.CN10_2 (PC8)
unnamed: J6.2, U1.CN10_1 (PC9)
unnamed: J7.2, U1.CN10_19 (PC7)
unnamed: J8.2, U1.CN10_29 (PB5)
unnamed: J8.3, U1.CN10_27 (PB4)
unnamed: J8.4, U1.CN10_15 (PA7)
unnamed: J8.5, U1.CN10_13 (PA6)
unnamed: SW1.1, U1.CN7_14 (RESET)
